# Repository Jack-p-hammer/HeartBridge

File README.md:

# HeartBridge

Software, electronics, mechanical parts and simulation for HeartBridge, an automated CPR machine. The project started as MIT 2.009 Green Team's 2025 class project and has continued since.

## Repository layout

| Folder | Contents |
|---|---|
| [`Raspberry Pi code/`](Raspberry%20Pi%20code/) | The Python controller that runs on the Raspberry Pi: state machine, sensing, motor control (moteus), screen and audio prompts, tests and bench scripts. See its [README](Raspberry%20Pi%20code/README.md) for setup. |
| `hardware/pcb/main-board/` | KiCad project for the main CPR machine board, plus its fab outputs in `production/` |
| `hardware/pcb/mcu-board/` | KiCad project for the MCU board |
| `hardware/pcb/contactor-board/` | KiCad project for the contactor board |
| `hardware/pcb/single-pager-legacy/` | Earlier single-sheet version of main board, kept for reference |
| `hardware/mechanical/` | 3D-print sources (`.step`, `.3mf`) for the current HeartBridge iteration |
| `simulation/` | Simulink model (`Heartbridge.slx`) and supporting MATLAB scripts. `legacy-m4/` holds the force sensor calibration from the class project. |
| `docs/` | Project documentation |

## Getting started

- **Controller code:** follow [`Raspberry Pi code/README.md`](Raspberry%20Pi%20code/README.md).
- **PCBs:** open the `.kicad_pro` file in a board's folder with KiCad. Custom symbol and footprint libraries live inside each board folder and are referenced relative to it.
- **Simulation:** in MATLAB, run `simulinkSetup.m` then open `Heartbridge.slx`.

## History

The repository was reorganized out of its class-project layout (`M3`–`M6`, `CPR Machine`, etc.) in October 2026. Older work is kept in tags rather than folders:

- `pre-restructure`: the last commit before the reorganization
- `archive/final`, `archive/integration`, `archive/zeroing`, `archive/hmi_v2`: class-era branches

To look at one, run `git checkout <tag>`. To keep working from one, create a branch: `git switch -c <name> <tag>`.

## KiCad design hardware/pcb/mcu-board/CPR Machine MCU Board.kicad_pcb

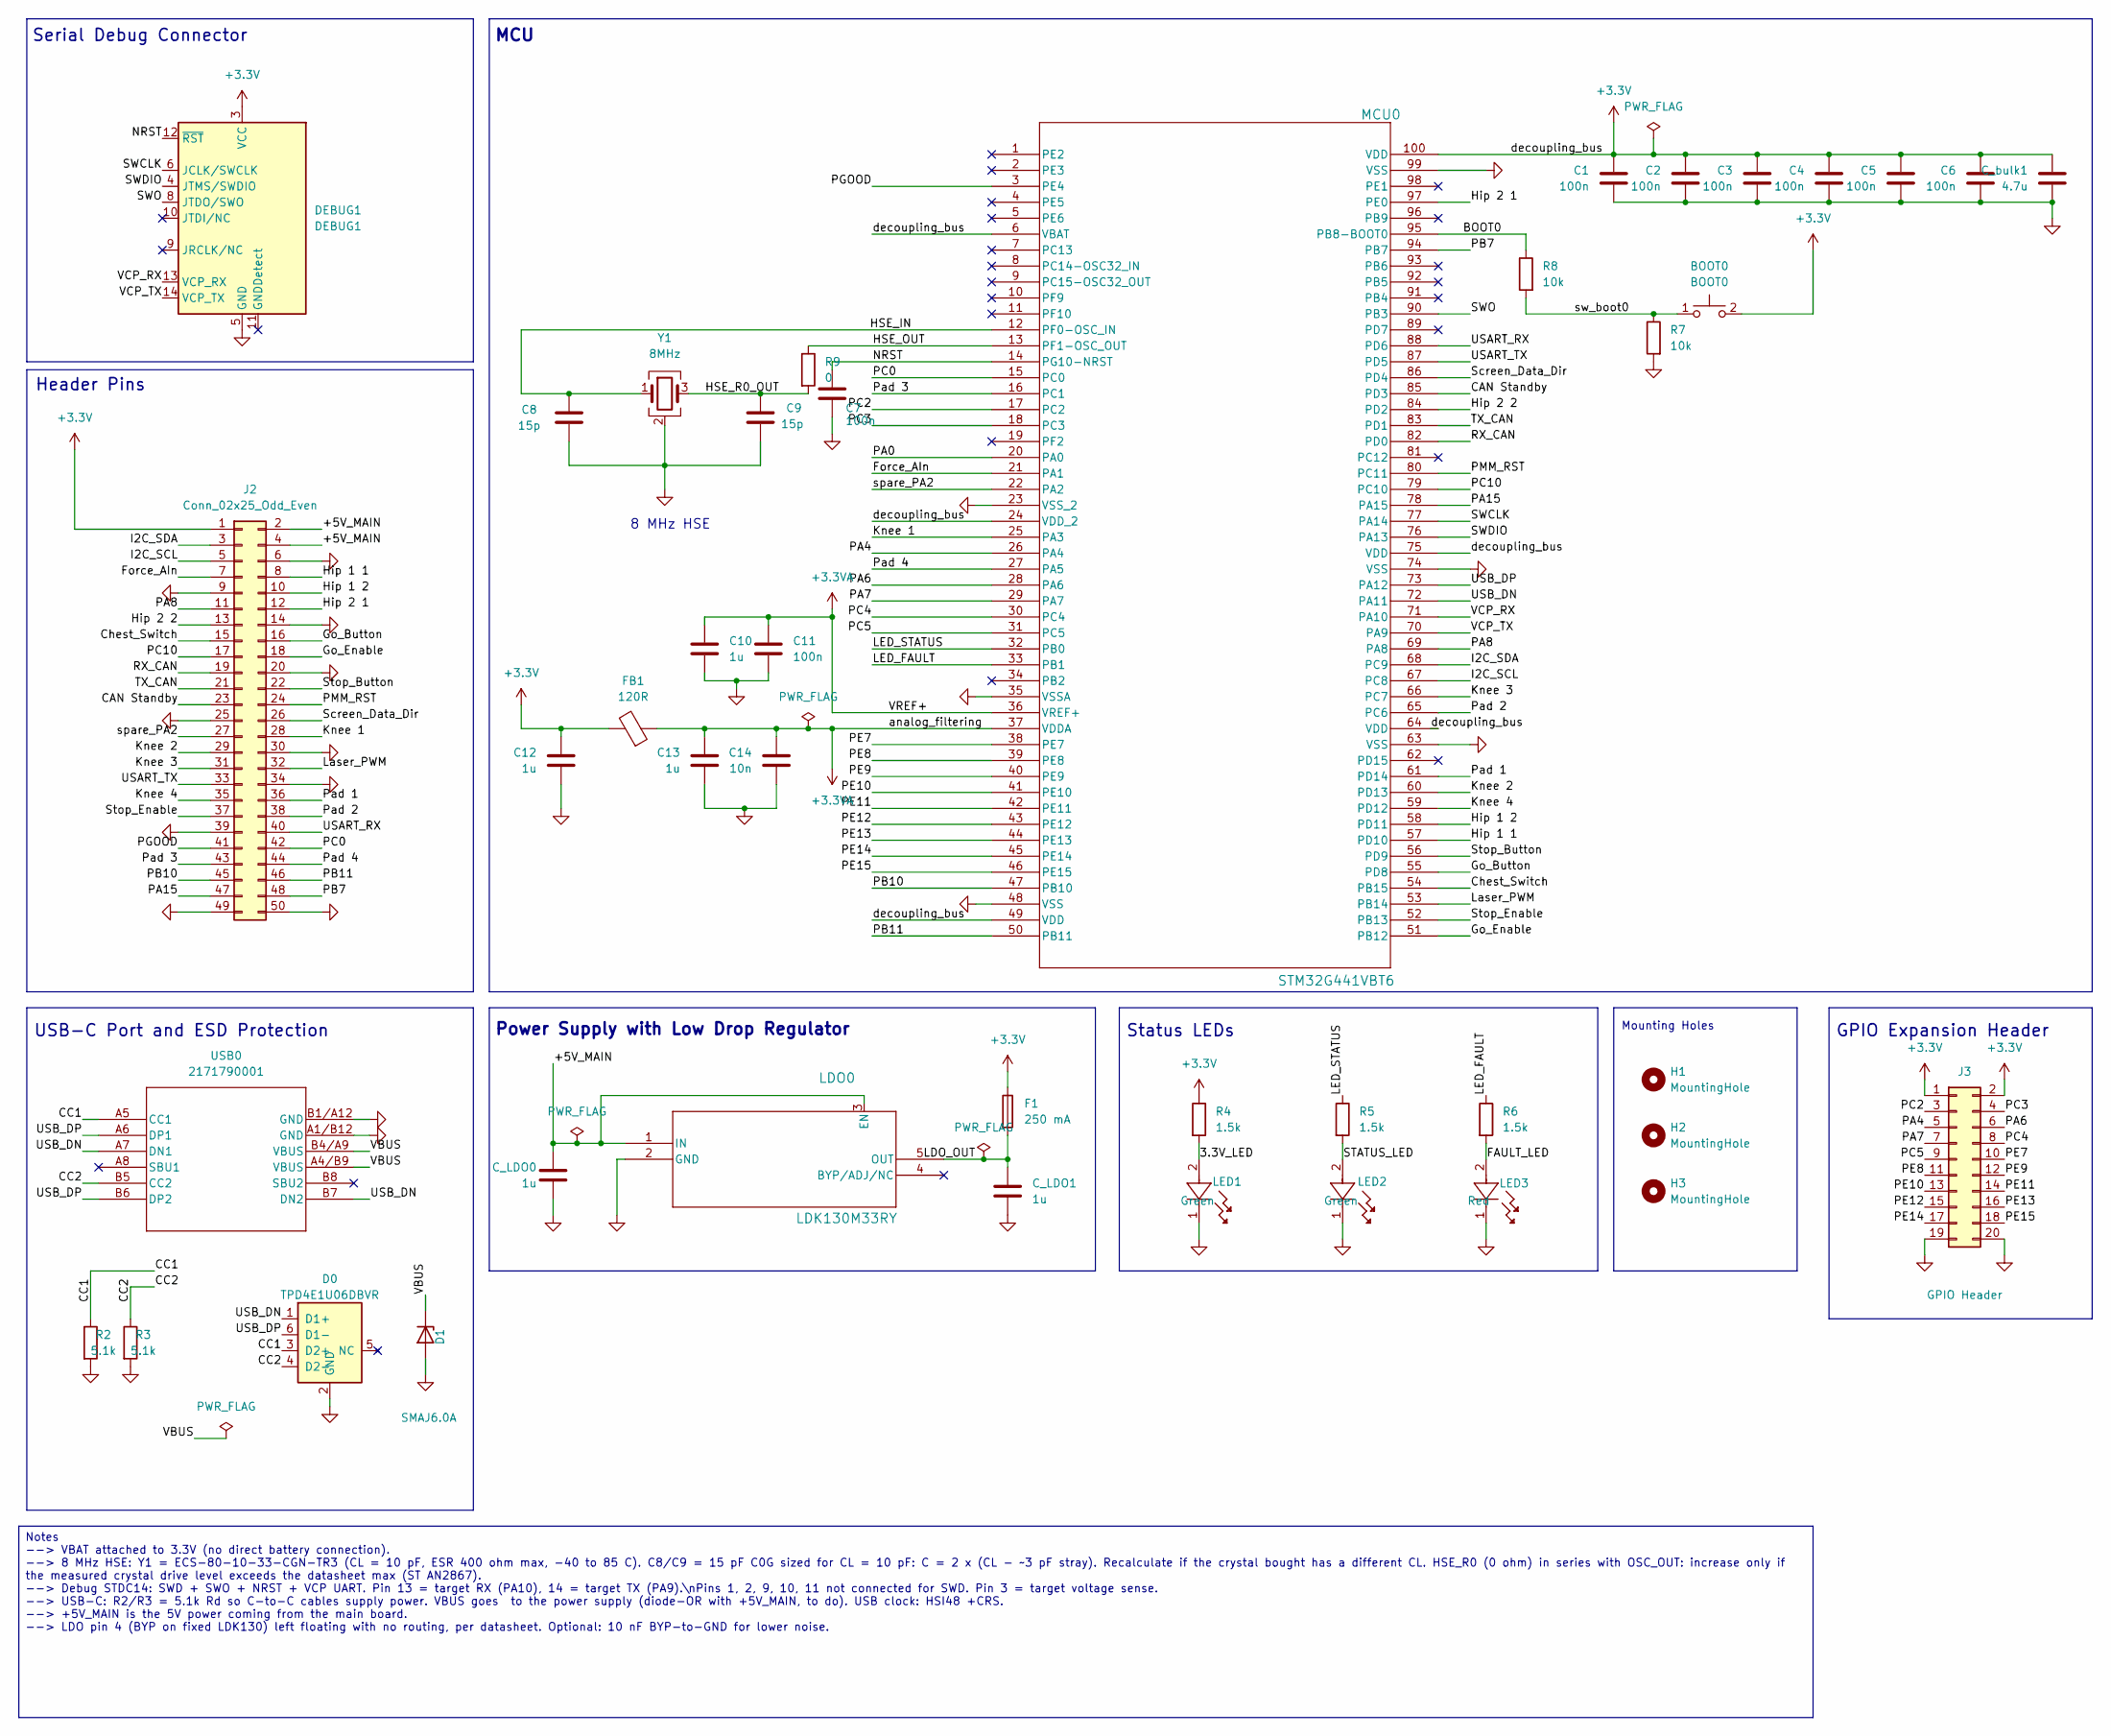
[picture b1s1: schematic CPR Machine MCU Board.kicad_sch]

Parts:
BOOT0: BOOT0; SW_SPST_PTS810; DigiKey Part Number CKN10502CT-ND
C1, C2, C3, C4, C5, C6, C7, C11: 100n; C_0603_1608Metric; DigiKey Part Number 399-C0603C104K4RACTUCT-ND
C8, C9: 15p; C_0603_1608Metric; DigiKey Part Number 399-C0603C150J5GACTUCT-ND
C10, C12, C13: 1u; C_0603_1608Metric; DigiKey Part Number 311-2082-1-ND
C14: 10n; C_0603_1608Metric; DigiKey Part Number 399-C0603C103K5RACTUCT-ND
C_LDO0, C_LDO1: 1u; C_0603_1608Metric; DigiKey Part Number 311-2082-1-ND
C_bulk1: 4.7u; C_0603_1608Metric; DigiKey Part Number 1276-1784-1-ND
D0: TPD4E1U06DBVR; SOT-23-6_Handsoldering; DigiKey Part Number 296-35965-1-ND
D1: SMAJ6.0A; D_SMA; DigiKey Part Number SMAJ6.0ALFCT-ND
DEBUG1: DEBUG1; PinHeader_2x07_P1.27mm_Vertical_SMD; DigiKey Part Number SAM9449-ND
F1: 250 mA; Fuse_1206_3216Metric_Pad1.42x1.75mm_HandSolder; DigiKey Part Number 5923-C1F250CT-ND
FB1: 120R; L_0603_1608Metric; DigiKey Part Number 490-1037-1-ND
H1, H2, H3: MountingHole; MountingHole_2.7mm_M2.5_Pad
J2: Conn_02x25_Odd_Even; PinSocket_2x25_P2.54mm_Vertical; DigiKey Part Number S7128-ND
J3: GPIO Header; PinHeader_2x10_P2.54mm_Vertical; DigiKey Part Number S2011EC-10-ND
LDO0: LDK130M33RY; SOT23-5L_STM; DigiKey Part Number 497-17800-1-ND
LED1, LED2: Green; LED_0603_1608Metric; DigiKey Part Number 160-1446-1-ND
LED3: Red; LED_0603_1608Metric; DigiKey Part Number 160-1447-1-ND
MCU0: STM32G441VBT6; LQFP100-14x14mm_STM; DigiKey Part Number 497-STM32G441VBT6-ND
R2, R3: 5.1k; R_0603_1608Metric; DigiKey Part Number 541-5.10KHCT-ND
R4, R5, R6: 1.5k; R_0603_1608Metric; DigiKey Part Number RMCF0603FT1K50CT-ND
R7, R8: 10k; R_0603_1608Metric; DigiKey Part Number 541-10.0KHCT-ND
R9: 0; R_0603_1608Metric; DigiKey Part Number RMCF0603ZT0R00CT-ND
USB0: 2171790001; 2171790001_MOL; DigiKey Part Number 900-2171790001CT-ND
Y1: 8MHz; Crystal_SMD_3225-4Pin_3.2x2.5mm; DigiKey Part Number 50-ECS-80-10-33-CGN-TR3CT-ND

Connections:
+3.3V: BOOT0.2, C1.1, C2.1, C3.1, C4.1, C5.1, C6.1, C12.1, C_bulk1.1, DEBUG1.3 (VCC), F1.1, FB1.2, J2.1, J3.1, J3.2, MCU0.6 (VBAT), MCU0.24 (VDD_2), MCU0.49 (VDD), MCU0.64 (VDD), MCU0.75 (VDD), MCU0.100 (VDD), R4.1
+3.3VA: C10.1, C11.1, C13.1, C14.1, FB1.1, MCU0.36 (VREF+), MCU0.37 (VDDA)
/3.3V_LED: LED1.2, R4.2
/+5V_MAIN: C_LDO0.1, J2.2, J2.4, LDO0.1 (IN), LDO0.3 (EN)
/BOOT0: MCU0.95 (PB8-BOOT0), R8.1
/CAN Standby: J2.23, MCU0.85 (PD3)
/CC1: D0.3 (D2+), R2.1, USB0.A5 (CC1)
/CC2: D0.4 (D2-), R3.1, USB0.B5 (CC2)
/Chest_Switch: J2.15, MCU0.54 (PB15)
/FAULT_LED: LED3.2, R6.2
/Force_AIn: J2.7, MCU0.21 (PA1)
/Go_Button: J2.16, MCU0.55 (PD8)
/Go_Enable: J2.18, MCU0.51 (PB12)
/HSE_IN: C8.1, MCU0.12 (PF0-OSC_IN), Y1.1
/HSE_OUT: MCU0.13 (PF1-OSC_OUT), R9.1
/HSE_R0_OUT: C9.1, R9.2, Y1.3
/Hip 1 1: J2.8, MCU0.57 (PD10)
/Hip 1 2: J2.10, MCU0.58 (PD11)
/Hip 2 1: J2.12, MCU0.97 (PE0)
/Hip 2 2: J2.13, MCU0.84 (PD2)
/I2C_SCL: J2.5, MCU0.67 (PC8)
/I2C_SDA: J2.3, MCU0.68 (PC9)
/Knee 1: J2.28, MCU0.25 (PA3)
/Knee 2: J2.29, MCU0.60 (PD13)
/Knee 3: J2.31, MCU0.66 (PC7)
/Knee 4: J2.35, MCU0.59 (PD12)
/LDO_OUT: C_LDO1.1, F1.2, LDO0.5 (OUT)
/LED_FAULT: MCU0.33 (PB1), R6.1
/LED_STATUS: MCU0.32 (PB0), R5.1
/Laser_PWM: J2.32, MCU0.53 (PB14)
/NRST: C7.1, DEBUG1.12 (~RST), MCU0.14 (PG10-NRST)
/PA0: MCU0.20 (PA0)
/PA4: J3.5, MCU0.26 (PA4)
/PA6: J3.6, MCU0.28 (PA6)
/PA7: J3.7, MCU0.29 (PA7)
/PA8: J2.11, MCU0.69 (PA8)
/PA15: J2.47, MCU0.78 (PA15)
/PB7: J2.48, MCU0.94 (PB7)
/PB10: J2.45, MCU0.47 (PB10)
/PB11: J2.46, MCU0.50 (PB11)
/PC0: J2.42, MCU0.15 (PC0)
/PC2: J3.3, MCU0.17 (PC2)
/PC3: J3.4, MCU0.18 (PC3)
/PC4: J3.8, MCU0.30 (PC4)
/PC5: J3.9, MCU0.31 (PC5)
/PC10: J2.17, MCU0.79 (PC10)
/PE7: J3.10, MCU0.38 (PE7)
/PE8: J3.11, MCU0.39 (PE8)
/PE9: J3.12, MCU0.40 (PE9)
/PE10: J3.13, MCU0.41 (PE10)
/PE11: J3.14, MCU0.42 (PE11)
/PE12: J3.15, MCU0.43 (PE12)
/PE13: J3.16, MCU0.44 (PE13)
/PE14: J3.17, MCU0.45 (PE14)
/PE15: J3.18, MCU0.46 (PE15)
/PGOOD: J2.41, MCU0.3 (PE4)
/PMM_RST: J2.24, MCU0.80 (PC11)
/Pad 1: J2.36, MCU0.61 (PD14)
/Pad 2: J2.38, MCU0.65 (PC6)
/Pad 3: J2.43, MCU0.16 (PC1)
/Pad 4: J2.44, MCU0.27 (PA5)
/RX_CAN: J2.19, MCU0.82 (PD0)
/STATUS_LED: LED2.2, R5.2
/SWCLK: DEBUG1.6 (JCLK/SWCLK), MCU0.77 (PA14)
/SWDIO: DEBUG1.4 (JTMS/SWDIO), MCU0.76 (PA13)
/SWO: DEBUG1.8 (JTDO/SWO), MCU0.90 (PB3)
/Screen_Data_Dir: J2.26, MCU0.86 (PD4)
/Stop_Button: J2.22, MCU0.56 (PD9)
/Stop_Enable: J2.37, MCU0.52 (PB13)
/TX_CAN: J2.21, MCU0.83 (PD1)
/USART_RX: J2.40, MCU0.88 (PD6)
/USART_TX: J2.33, MCU0.87 (PD5)
/USB_DN: D0.1 (D1+), MCU0.72 (PA11), USB0.A7 (DN1), USB0.B7 (DN2)
/USB_DP: D0.6 (D1-), MCU0.73 (PA12), USB0.A6 (DP1), USB0.B6 (DP2)
/VBUS: D1.1 (K), USB0.A4/B9 (VBUS), USB0.B4/A9 (VBUS)
/VCP_RX: DEBUG1.13 (VCP_RX), MCU0.71 (PA10)
/VCP_TX: DEBUG1.14 (VCP_TX), MCU0.70 (PA9)
/spare_PA2: J2.27, MCU0.22 (PA2)
/sw_boot0: BOOT0.1, R7.1, R8.2
GND: C1.2, C2.2, C3.2, C4.2, C5.2, C6.2, C7.2, C8.2, C9.2, C10.2, C11.2, C12.2, C13.2, C14.2, C_LDO0.2, C_LDO1.2, C_bulk1.2, D0.2 (GND), D1.2 (A), DEBUG1.5 (GND), DEBUG1.7 (GND), J2.6, J2.9, J2.14, J2.20, J2.25, J2.30, J2.34, J2.39, J2.49, J2.50, J3.19, J3.20, LDO0.2 (GND), LED1.1, LED2.1, LED3.1, MCU0.23 (VSS_2), MCU0.35 (VSSA), MCU0.48 (VSS), MCU0.63 (VSS), MCU0.74 (VSS), MCU0.99 (VSS), R2.2, R3.2, R7.2, USB0.A1/B12 (GND), USB0.B1/A12 (GND), Y1.2 (G), Y1.4 (G)

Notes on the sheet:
Mounting Holes
Status LEDs
USB-C Port and ESD Protection
GPIO Expansion Header
8 MHz HSE
Serial Debug Connector
Power Supply with Low Drop Regulator
Header Pins
MCU
Notes --> VBAT attached to 3.3V (no direct battery connection). --> 8 MHz HSE: Y1 = ECS-80-10-33-CGN-TR3 (CL = 10 pF, ESR 400 ohm max, -40 to 85 C). C8/C9 = 15 pF C0G sized for CL = 10 pF: C = 2 x (CL - ~3 pF stray). Recalculate if the crystal bought has a different CL. HSE_R0 (0 ohm) in series wit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

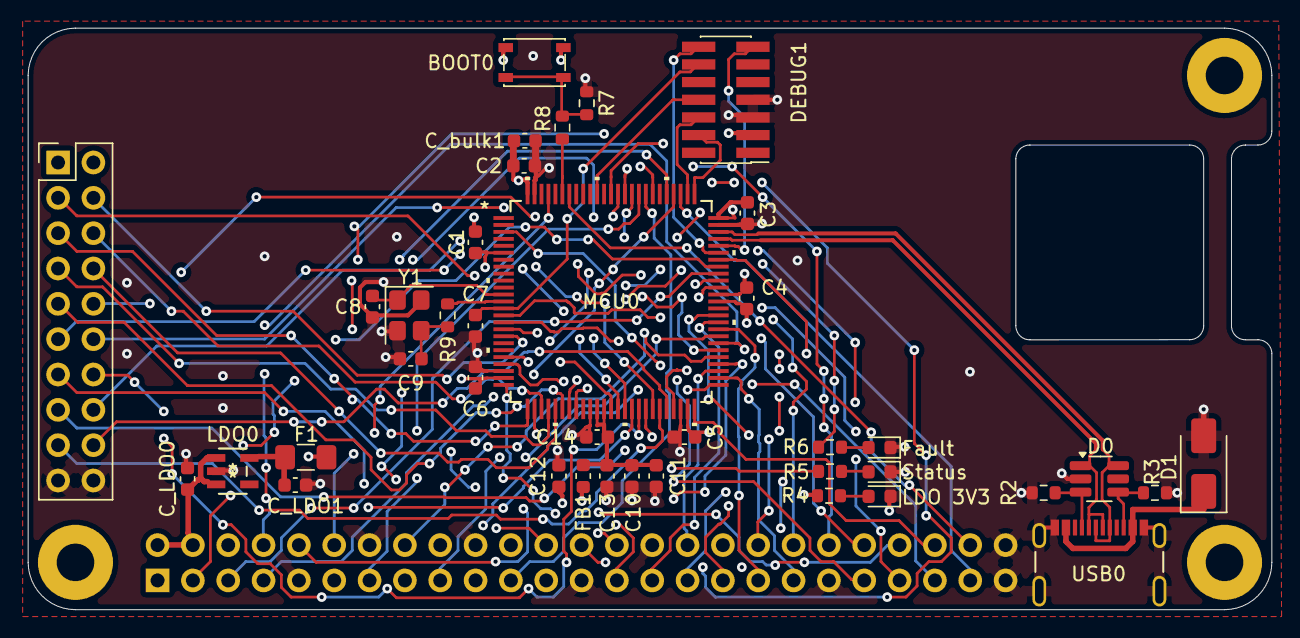
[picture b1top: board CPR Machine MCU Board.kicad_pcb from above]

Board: 4 copper layers, 89.4 x 41.8 mm, 43 parts (1 on the bottom side), 79 nets.

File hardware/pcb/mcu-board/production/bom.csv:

Designator,Footprint,Quantity,Value,LCSC Part #
BOOT0,SW_SPST_PTS810,1,BOOT0,
"C1, C11, C2, C3, C4, C5, C6, C7",0603,8,100n,
"C10, C12, C13, C_LDO0, C_LDO1",0603,5,1u,
C14,0603,1,10n,
"C8, C9",0603,2,15p,
C_BULK1,0603,1,4.7u,
D0,SOT-23-6_Handsoldering,1,TPD4E1U06DBVR,
D1,D_SMA,1,SMAJ6.0A,
DEBUG1,PinHeader_2x07_P1.27mm_Vertical_SMD,1,DEBUG1,
F1,1206,1,250 mA,
FB1,0603,1,120R,
J2,PinSocket_2x25_P2.54mm_Vertical,1,Conn_02x25_Odd_Even,
J3,PinHeader_2x10_P2.54mm_Vertical,1,GPIO Header,
LDO0,SOT23-5L_STM,1,LDK130M33RY,
"LED1, LED2",0603,2,Green,
LED3,0603,1,Red,
MCU0,LQFP100-14x14mm_STM,1,STM32G441VBT6,
"R2, R3",0603,2,5.1k,
"R4, R5, R6",0603,3,1.5k,
"R7, R8",0603,2,10k,
R9,0603,1,0,
USB0,2171790001_MOL,1,2171790001,
Y1,Crystal_SMD_3225-4Pin_3.2x2.5mm,1,8MHz,

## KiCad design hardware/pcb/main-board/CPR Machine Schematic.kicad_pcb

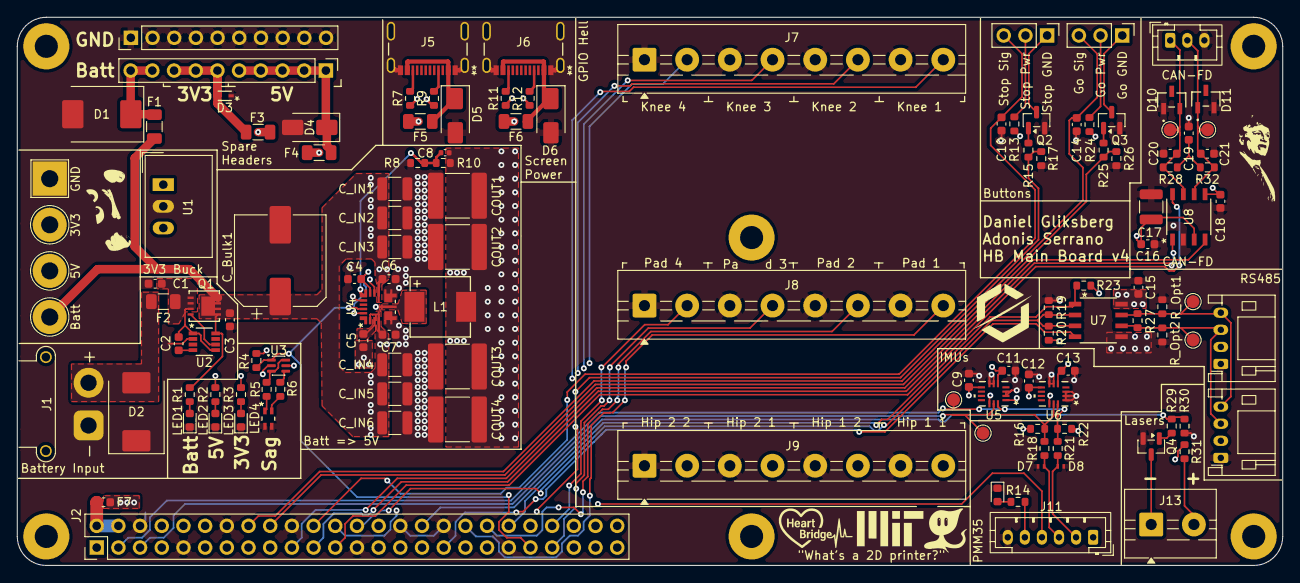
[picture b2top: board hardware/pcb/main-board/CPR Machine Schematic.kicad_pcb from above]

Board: 6 copper layers, 148.2 x 64.2 mm, 133 parts (0 on the bottom side), 74 nets.

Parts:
C1: 47 nF; C_0603_1608Metric
C2, C3, C5, C9, C10, C11, C12, C13, C14, C15, C16, C18: 0.1 uF; C_0603_1608Metric
C4: 2.2 uF; C_0603_1608Metric
C6, C7: 1 uF; C_0603_1608Metric
C8: 100 pF; C_0402_1005Metric
C17: 10 uF; C_1210_3225Metric
C19: 4.7 nF; C_0603_1608Metric
C20, C21: 47 pF; C_0603_1608Metric
COUT1, COUT2, COUT3, COUT4: 47 uF; C_2220_5750Metric
C_Bulk1: 100 uF; CP_Elec_10x10.5
C_IN1, C_IN2, C_IN3, C_IN4, C_IN5, C_IN6: 10 uF; C_1210_3225Metric
D1: SMCJ28A; D_SMC
D2: SMCJ28CA; D_SMC
D3: ESD321DYAR; SOT5x3_DYA_TEX
D4, D5, D6: SMAJ6.0A; D_SMA
D7, D8: ESD351DPYR; DPY2_TEX
D10, D11: MMBZ27VCLT1G; SOT-23-3_1P4X3P040_ONS
F1, F2, F4: 1A; Fuse_1206_3216Metric
F3, F5, F6: 1.5A; Fuse_1206_3216Metric
F7: 0.25A; Fuse_0603_1608Metric
H1, H2, H3, H4, H5, H6: MountingHole; MountingHole_2.7mm_M2.5_Pad
J1: Battery IN; AMASS_XT30PW-F_1x02_P2.50mm_Horizontal
J2: Conn_02x25_Odd_Even; PinHeader_2x25_P2.54mm_Vertical
J3: GND Spare Headers; PinHeader_1x10_P2.54mm_Vertical
J4: +V Spare Headers; PinHeader_1x10_P2.54mm_Vertical
J5, J6: 2171790001; 2171790001_MOL
J7: Knee; TerminalBlock_MaiXu_MX126-5.0-08P_1x08_P5.00mm
J8: Pads; TerminalBlock_MaiXu_MX126-5.0-08P_1x08_P5.00mm
J9: Hip; TerminalBlock_MaiXu_MX126-5.0-08P_1x08_P5.00mm
J10: Stop Button Port; PinHeader_1x03_P2.54mm_Vertical
J11: PMM Port; JST_PH_B6B-PH-K_1x06_P2.00mm_Vertical
J12: Go Button Port; PinHeader_1x03_P2.54mm_Vertical
J13: Laser Port; TerminalBlock_MaiXu_MX126-5.0-02P_1x02_P5.00mm
J14: CAN-FD Port; JST_PH_B3B-PH-K_1x03_P2.00mm_Vertical
J15, J16: RS485 Port; JST_PH_S4B-PH-K_1x04_P2.00mm_Horizontal
L1: 3.3 uH; IND_CCDS-3R3MC_SUM
LED1, LED2, LED3, LED5: Green; LED_0603_1608Metric
LED4: APHBM2012LSURKZGKC; APHBM2012LSURKZGKC_KNB
Q1: DMT6007LFG-7; TRANS_DMT6007LFG-7_DIO
Q2, Q3, Q4: T2N7002BK,LM; SOT-23
R1, R17, R19, R20, R23, R26, R30: 10 kOhm; R_0603_1608Metric
R2, R14: 680 Ohm; R_0603_1608Metric
R3: 270 Ohm; R_0603_1608Metric
R4, R10: 49.9 kOhm; R_0603_1608Metric
R5: 750 Ohm; R_0603_1608Metric
R6: 301 Ohm; R_0603_1608Metric
R7, R9, R11, R12: 22 kOhm; R_0603_1608Metric
R8: 9.31 kOhm; R_0603_1608Metric
R13, R24: 49.9 Ohm; R_0603_1608Metric
R15, R25, R29: 100 Ohm; R_0603_1608Metric
R16, R22: 2.2k; R_0603_1608Metric
R18, R21: 33 Ohm; R_0603_1608Metric
R27: 120 Ohm; R_0603_1608Metric
R28, R32: 60.4 Ohm; R_0603_1608Metric
R31: 0 Ohm; R_0603_1608Metric
R_Opt1, R_Opt2: 10 kOhm; R_0603_1608Metric
TP1: GND; TestPoint_THTPad_4.0x4.0mm_Drill2.0mm
TP2: 3V3; TestPoint_THTPad_D4.0mm_Drill2.0mm
TP3: 5 V; TestPoint_THTPad_D4.0mm_Drill2.0mm
TP4: Battery; TestPoint_THTPad_D4.0mm_Drill2.0mm
TP5: SDA; TestPoint_Pad_D1.5mm
TP6: SCL; TestPoint_Pad_D1.5mm
TP7: CANH; TestPoint_Pad_D1.5mm
TP8: RS485_B; TestPoint_Pad_D1.5mm
TP9: RS485_A; TestPoint_Pad_D1.5mm
TP10: CANL; TestPoint_Pad_D1.5mm
U1: 3.3V Buck; Converter_DCDC_TRACO_TSR-1_THT
U2: LM74700MDDFREP; SOT23_DDF_TEX
U3: 74LVC2G04; SOT-363_SC-70-6
U4: MAX42406AFOB+; 21-100700_90-100240_ADI
U5, U6: LSM6DSV16XTR; LGA-14L_STM
U7: THVD1439DR; D8_TEX
U8: ATA6563-GAQW1; SOIC8_SN_MCH

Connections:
+3.3V: C9.2, C11.2, C12.2, C13.2, C15.2, C18.2, F3.2, R3.2, R4.1, R16.2, R20.2, R22.1, R23.2, R31.1, TP2.1 (1_1), U1.3 (Vout), U3.5 (VCC), U5.1 (SDO/SA0), U5.5 (VDD_IO), U5.8 (VDD), U5.12 (CS), U6.5 (VDD_IO), U6.8 (VDD), U6.12 (CS), U7.8 (VCC), U8.5 (VIO)
+5V: C8.1, C16.2, C17.2, COUT1.1, COUT2.1, COUT3.1, COUT4.1, F4.2, F5.1, F6.1, F7.1, L1.2, R2.2, R7.1, R9.2, R10.1, R11.1, R12.2, R13.2, R24.2, TP3.1 (1_1), U1.1 (Vin), U4.13 (OUT), U8.3 (VCC)
+22.2V: C3.2, C6.2, C7.2, C_Bulk1.1, C_IN1.2, C_IN2.2, C_IN3.2, C_IN4.2, C_IN5.2, C_IN6.2, F1.2, Q1.5, Q1.6, Q1.7, Q1.8, R1.2, TP4.1 (1_1), U2.8 (CATHODE), U4.1 (EN), U4.3 (SUP), U4.9 (SUP)
/HMI/Go Button: C14.2, J2.16, J12.3
/HMI/Go Button Ground: J12.1, Q3.3 (D)
/HMI/Go LED Power: J12.2, R24.1
/HMI/Go_Enable: J2.18, R25.1, R26.1
/HMI/Laser_PWM: J2.32, R29.1, R30.1
/HMI/RS485_A: J15.3, J16.3, R27.1, R_Opt2.2, TP9.1 (1_1), U7.6 (A)
/HMI/RS485_B: J15.4, J16.4, R27.2, R_Opt1.1, TP8.1 (1_1), U7.7 (B)
/HMI/Screen_Data_Dir: J2.26, R19.2, R20.1, U7.2 (*RE), U7.3 (DE)
/HMI/Stop Button: C10.2, J2.22, J10.3
/HMI/Stop Button Ground: J10.1, Q2.3 (D)
/HMI/Stop LED Power: J10.2, R13.1
/HMI/Stop_Enable: J2.37, R15.1, R17.1
/HMI/USART_RX: J2.40, R23.1, U7.1 (R)
/HMI/USART_TX: J2.33, U7.4 (D)
/MCU Connector/CAN Standby: J2.23, U8.8 (STBY)
/MCU Connector/Hip 1 1: J2.8, J9.8
/MCU Connector/Hip 1 2: J2.10, J9.6
/MCU Connector/Hip 2 1: J2.12, J9.4
/MCU Connector/Hip 2 2: J2.13, J9.2
/MCU Connector/I2C_SCL: J2.5, R16.1, R18.1, TP6.1 (1_1), U5.13 (SCL), U6.13 (SCL)
/MCU Connector/I2C_SDA: J2.3, R21.2, R22.2, TP5.1 (1_1), U5.14 (SDA), U6.14 (SDA)
/MCU Connector/Knee 1: J2.28, J7.8
/MCU Connector/Knee 2: J2.29, J7.6
/MCU Connector/Knee 3: J2.31, J7.4
/MCU Connector/Knee 4: J2.35, J7.2
/MCU Connector/PMM_RST: J2.24, J11.4
/MCU Connector/Pad 1: J2.36, J8.8
/MCU Connector/Pad 2: J2.38, J8.6
/MCU Connector/Pad 3: J2.43, J8.4
/MCU Connector/Pad 4: J2.44, J8.2
/MCU Connector/RX_CAN: J2.19, U8.4 (RXD)
/MCU Connector/TX_CAN: J2.21, U8.1 (TXD)
/Motors/CANH+: C20.1, D10.2 (K2), J14.1, R28.2, TP7.1 (1_1), U8.7 (CANH)
/Motors/CANL-: C21.2, D11.1 (K1), J14.2, R32.1, TP10.1 (1_1), U8.6 (CANL)
/Power/0V Gate: Q1.4, U2.6 (GATE)
/Power/BIAS: C4.2, U4.11 (BIAS), U4.16 (SYNC)
/Power/BST: C5.1, U4.2 (BST)
/Power/Battery In: D2.2 (A2), F2.1, J1.2
/Power/FB: C8.2, R8.1, R10.2, U4.12 (FB)
/Power/LX: C5.2, L1.1, U4.6 (LX)
/Power/PGood: J2.41, R4.2, U3.1, U4.15 (PGOOD)
GND: C1.1, C3.1, C4.1, C6.1, C7.1, C9.1, C10.1, C11.1, C12.1, C13.1, C14.1, C15.1, C16.1, C17.1, C18.1, C19.1, C20.2, C21.1, COUT1.2, COUT2.2, COUT3.2, COUT4.2, C_Bulk1.2, C_IN1.1, C_IN2.1, C_IN3.1, C_IN4.1, C_IN5.1, C_IN6.1, D1.2 (A), D2.1 (A1), D3.1 (A), D4.2 (A), D5.2 (A), D6.2 (A), D7.2 (A), D8.2 (A), D10.1 (K1), D11.2 (K2), J1.1, J2.6, J2.9, J2.14, J2.20, J2.25, J2.30, J2.34, J2.39, J3.1, J3.2, J3.3, J3.4, J3.5, J3.6, J3.7, J3.8, J3.9, J3.10, J5.A1/B12 (GND), J5.B1/A12 (GND), J6.A1/B12 (GND), J6.B1/A12 (GND), J7.1, J7.3, J7.5, J7.7, J8.1, J8.3, J8.5, J8.7, J9.1, J9.3, J9.5, J9.7, J11.6, J14.3, J15.1, J16.1, LED1.1, LED2.1, LED3.1, LED4.2, LED4.3, LED5.1, Q2.2 (S), Q3.2 (S), Q4.2 (S), R8.2, R17.2, R19.1, R26.2, R30.2, R_Opt1.2, R_Opt2.1, TP1.1 (1_1), U1.2 (GND), U2.2 (GND), U3.2 (GND), U4.4 (PGND), U4.5 (PGND), U4.7 (PGND), U4.8 (PGND), U4.10 (GND), U5.2 (SDX/AH1/QVAR1), U5.3 (SCX/AH2/QVAR2), U5.6 (GND), U5.7 (GND), U6.1 (SDO/SA0), U6.2 (SDX/AH1/QVAR1), U6.3 (SCX/AH2/QVAR2), U6.6 (GND), U6.7 (GND), U7.5 (GND), U8.2 (GND)
unnamed: C19.2, R28.1, R32.2
unnamed: D1.1 (K), F1.1, J4.9, J4.10
unnamed: D3.2 (K), F3.1, J4.6, J4.7, J4.8
unnamed: D4.1 (K), F4.1, J4.1, J4.2, J4.3, J4.4, J4.5
unnamed: D5.1 (K), F5.2, J5.A4/B9 (VBUS), J5.B4/A9 (VBUS)
unnamed: D6.1 (K), F6.2, J6.A4/B9 (VBUS), J6.B4/A9 (VBUS)
unnamed: D7.1 (K), J11.3, R18.2
unnamed: D8.1 (K), J11.2, R21.1
unnamed: F7.2, J2.2, J2.4
unnamed: J5.A5 (CC1), R9.1
unnamed: J5.B5 (CC2), R7.2
unnamed: J6.A5 (CC1), R12.1
unnamed: J6.B5 (CC2), R11.2
unnamed: J11.5, R14.1
unnamed: J13.1, Q4.3 (D)
unnamed: J13.2, R31.2
unnamed: LED1.2, R1.1
unnamed: LED2.2, R2.1
unnamed: LED3.2, R3.1
unnamed: LED4.1, R5.1
unnamed: LED4.4, R6.1
unnamed: LED5.2, R14.2
unnamed: Q2.1 (G), R15.2
unnamed: Q3.1 (G), R25.2
unnamed: Q4.1 (G), R29.2
unnamed: R5.2, U3.3, U3.6
unnamed: R6.2, U3.4
unnamed: C1.2, C2.2, F2.2, Q1.1, Q1.2, Q1.3, U2.1 (EN), U2.5 (ANODE)
unnamed: C2.1, U2.4 (VCAP)

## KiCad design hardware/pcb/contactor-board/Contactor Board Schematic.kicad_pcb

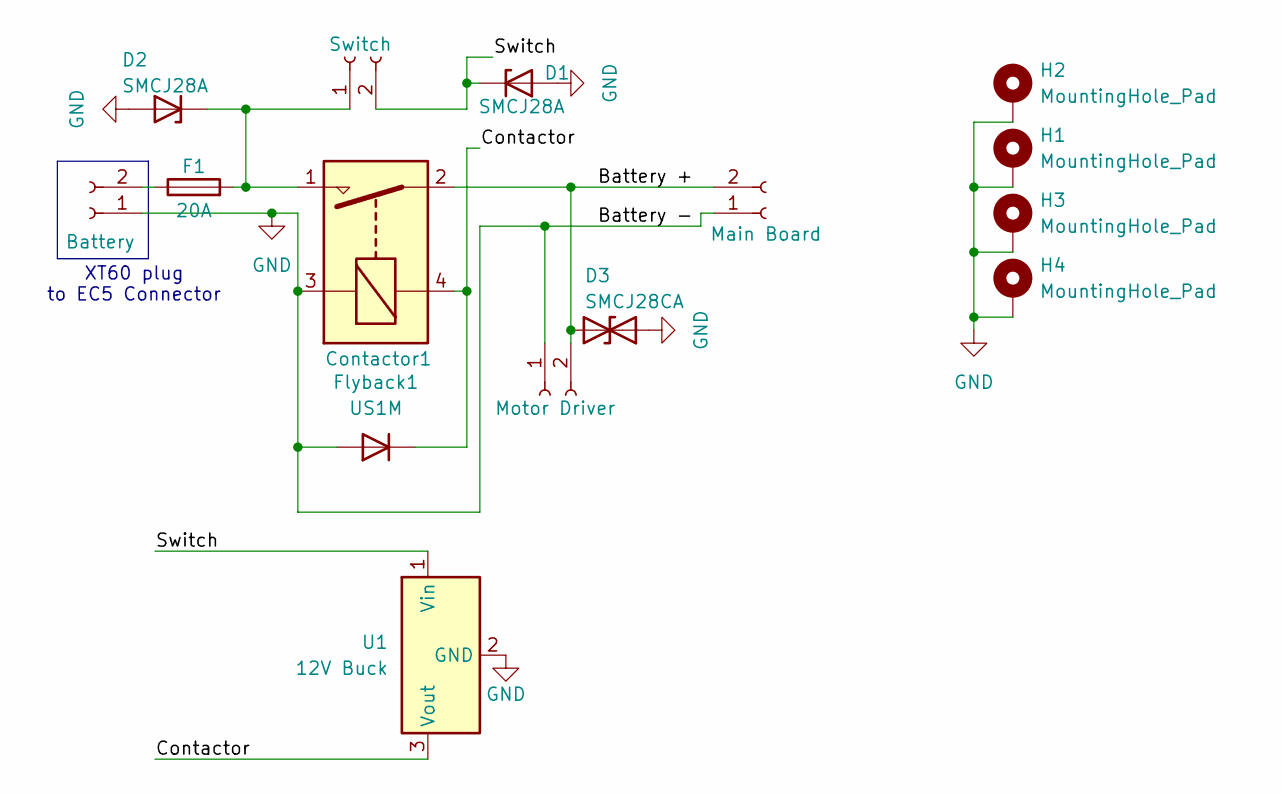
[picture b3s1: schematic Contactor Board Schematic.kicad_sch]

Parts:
Contactor1: AEV20E-BP; AEV20EBP; digikey 2040-AEV20E-BP-ND
D1, D2: SMCJ28A; D_SMC; digikey SMCJ28ALFCT-ND
D3: SMCJ28CA; D_SMC; digikey SMCJ28CALFCT-ND
F1: 20A; Fuse_1206_3216Metric; digikey 5923-0685H9200-01CT-ND
Flyback1: US1M; D_SMA; digikey 4878-US1MCT-ND
H1, H2, H3, H4: MountingHole_Pad; MountingHole_2.7mm_Pad
J_EXT1: Main Board; AMASS_XT30U-M_1x02_P5.0mm_Vertical
J_EXT2: Battery; AMASS_XT60-M_1x02_P7.20mm_Vertical
J_EXT3: Motor Driver; AMASS_XT30U-M_1x02_P5.0mm_Vertical
J_EXT4: Switch; AMASS_XT30U-M_1x02_P5.0mm_Vertical
U1: 12V Buck; Converter_DCDC_TRACO_TSR-1_THT; digikey 1951-2739-ND

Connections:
/Battery +: Contactor1.2, D3.2 (A2), J_EXT1.2, J_EXT3.2
/Contactor: Contactor1.4, Flyback1.1 (K), U1.3 (Vout)
/Switch: D1.1 (K), J_EXT4.2, U1.1 (Vin)
GND: Contactor1.3, D1.2 (A), D2.2 (A), D3.1 (A1), Flyback1.2 (A), H1.1 (1_1), H2.1 (1_1), H3.1 (1_1), H4.1 (1_1), J_EXT1.1, J_EXT2.1, J_EXT3.1, U1.2 (GND)
unnamed: Contactor1.1, D2.1 (K), F1.2, J_EXT4.1
unnamed: F1.1, J_EXT2.2

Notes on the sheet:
XT60 plug to EC5 Connector

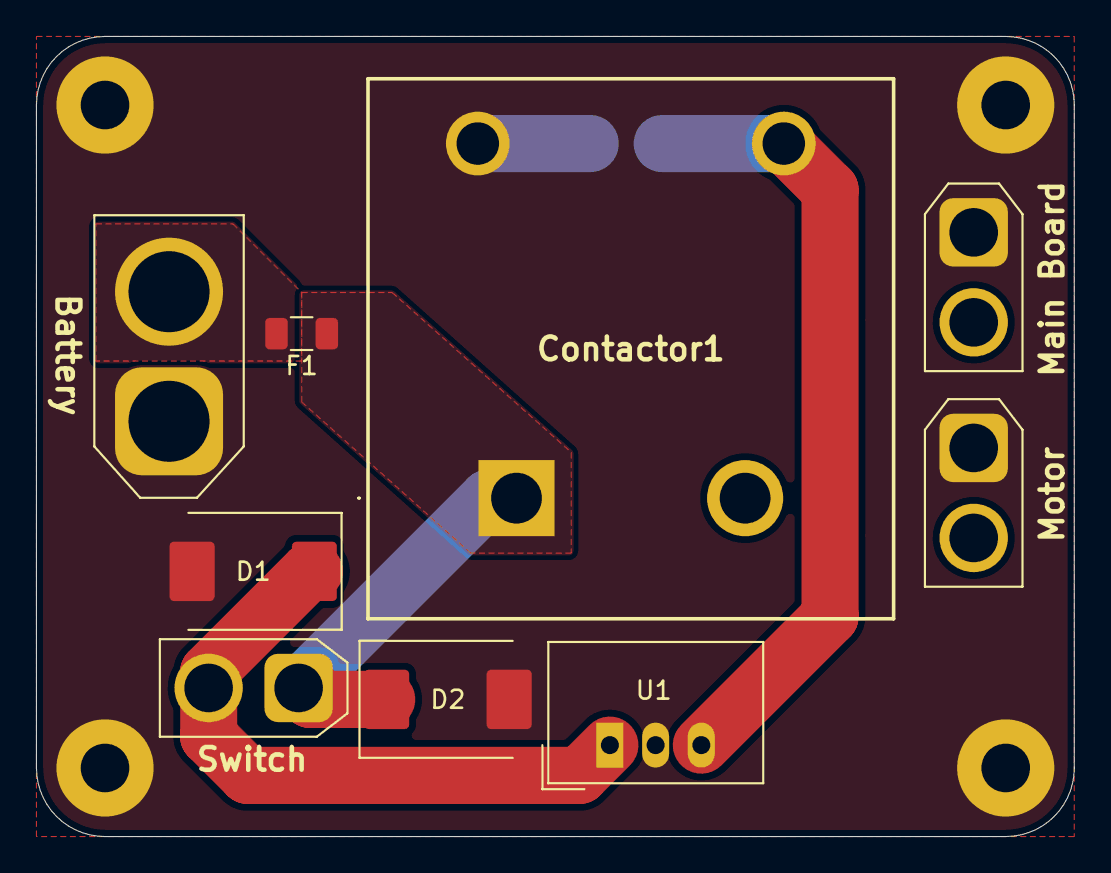
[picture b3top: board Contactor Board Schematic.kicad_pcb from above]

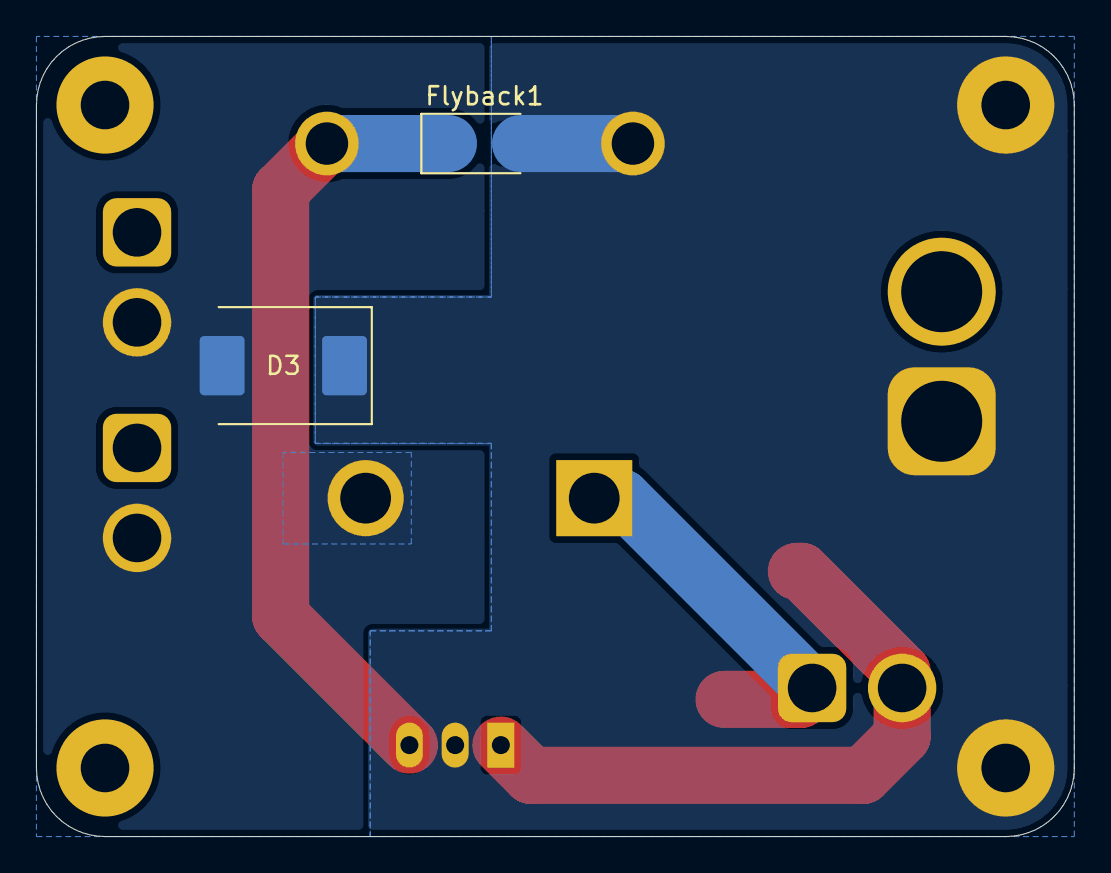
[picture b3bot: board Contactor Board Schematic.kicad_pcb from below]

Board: 2 copper layers, 57.7 x 44.5 mm, 15 parts (2 on the bottom side), 6 nets.

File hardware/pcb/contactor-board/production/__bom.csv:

Designator,Footprint,Quantity,Value,LCSC Part #
CONTACTOR1,AEV20EBP,1,AEV20E-BP,
"D1, D2",D_SMC,2,SMCJ28A,
D3,D_SMC,1,SMCJ28CA,
F1,1206,1,20A,
FLYBACK1,D_SMA,1,US1M,
J_EXT1,AMASS_XT30U-M_1x02_P5.0mm_Vertical,1,Main Board,
J_EXT2,AMASS_XT60-M_1x02_P7.20mm_Vertical,1,Battery,
J_EXT3,AMASS_XT30U-M_1x02_P5.0mm_Vertical,1,Motor Driver,
J_EXT4,AMASS_XT30U-M_1x02_P5.0mm_Vertical,1,Switch,
U1,Converter_DCDC_TRACO_TSR-1_THT,1,12V Buck,
